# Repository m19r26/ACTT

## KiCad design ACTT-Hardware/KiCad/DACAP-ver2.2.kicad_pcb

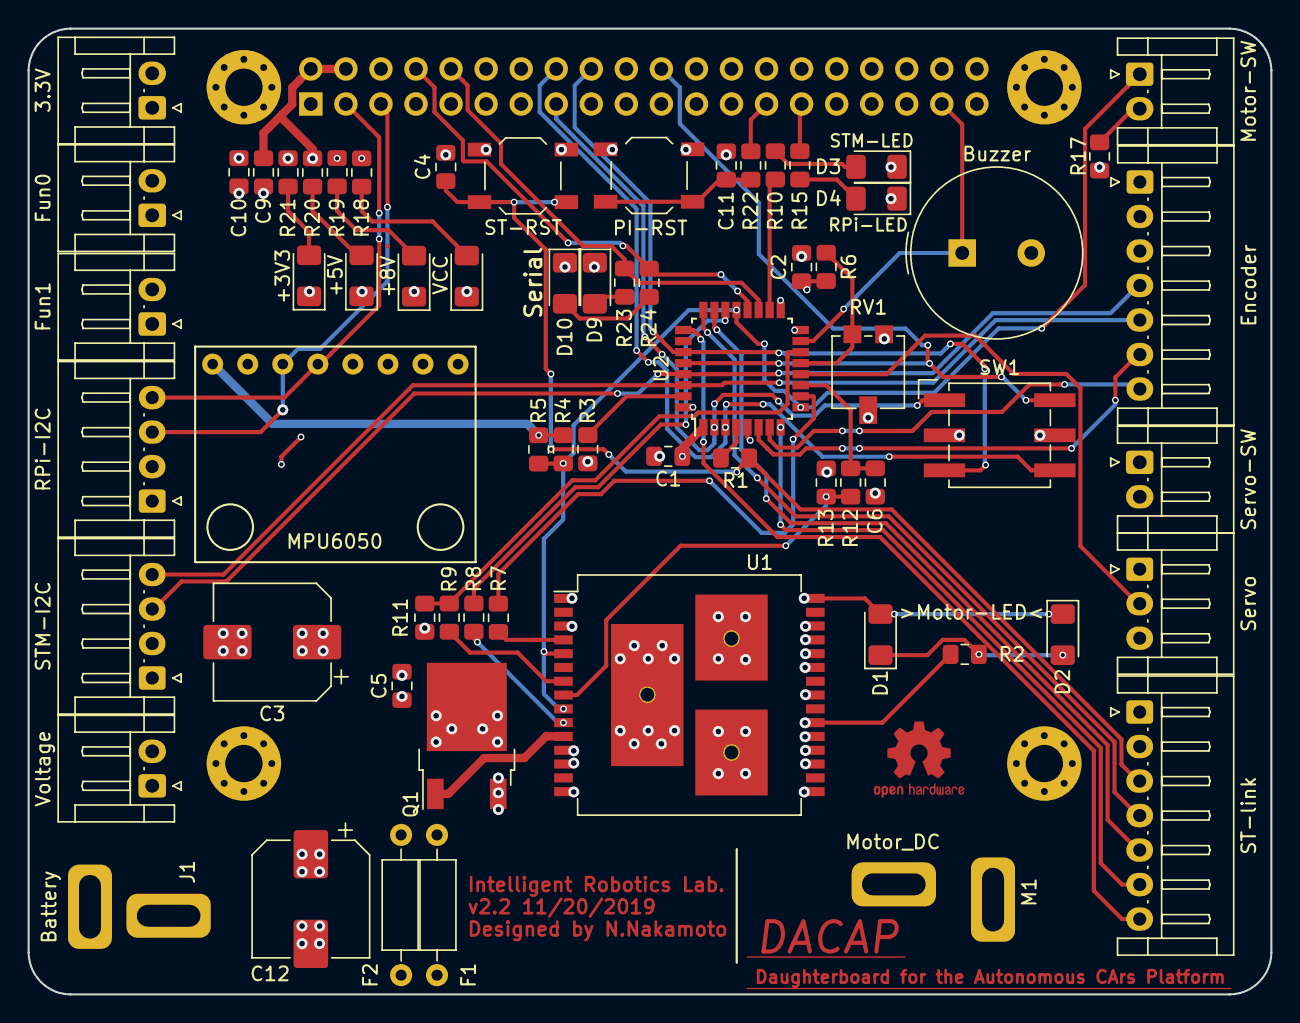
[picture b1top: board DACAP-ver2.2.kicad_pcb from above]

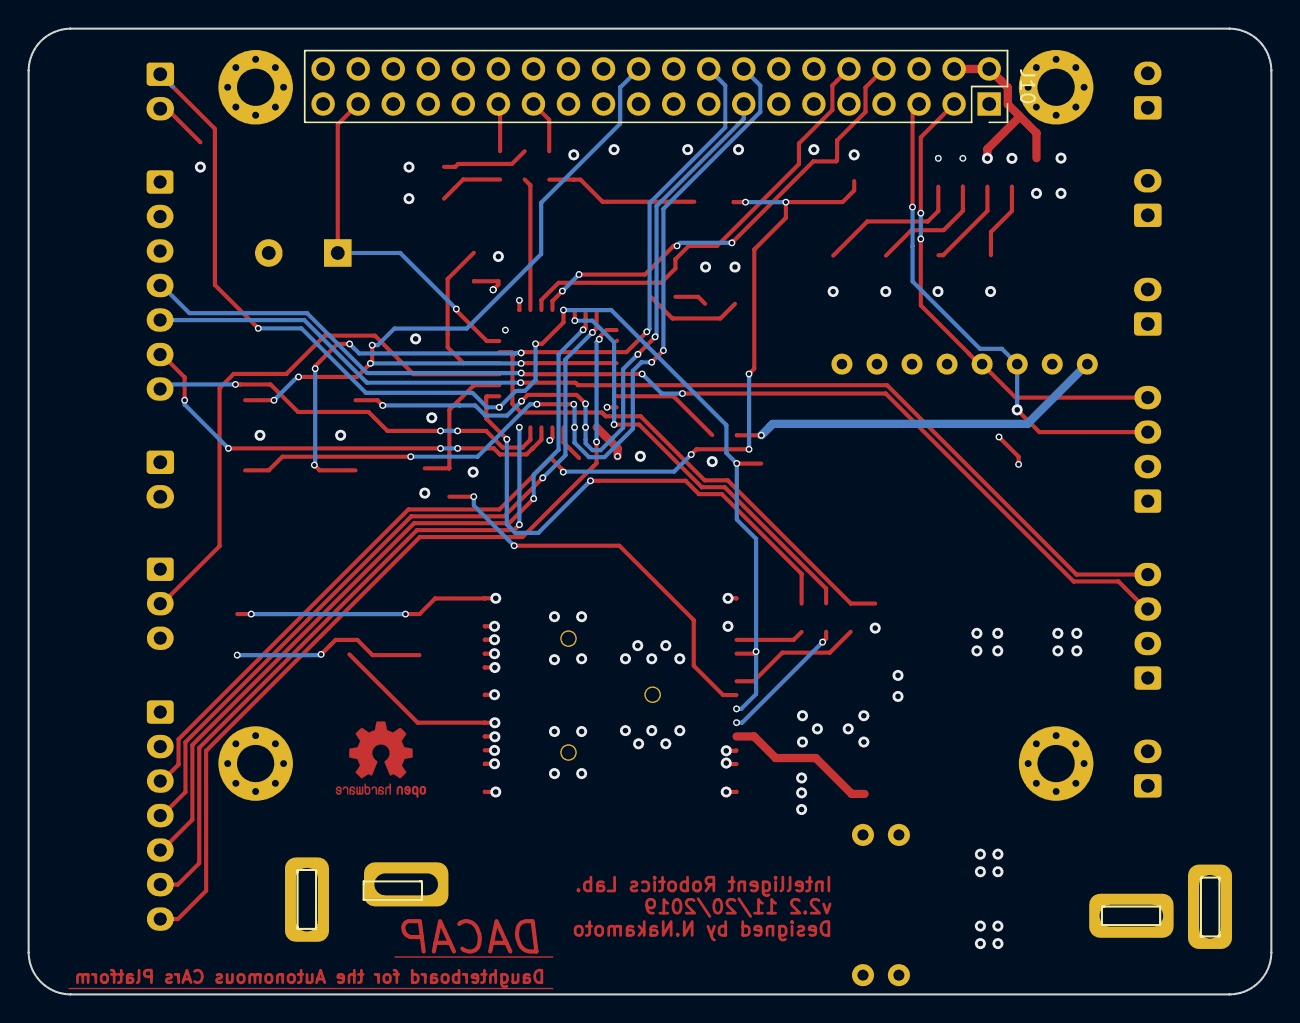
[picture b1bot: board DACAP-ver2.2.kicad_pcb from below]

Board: 4 copper layers, 90.0 x 70.0 mm, 71 parts (3 on the bottom side), 56 nets.

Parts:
3.3V: 3V3; JST_EH_S02B-EH_1x02_P2.50mm_Horizontal
Buzzer: PKM13EPYH4000-A0; Buzzer_TDK_PS1240P02BT_D12.2mm_H6.5mm
C1, C2, C4, C5, C6, C9, C10, C11: 0.1uF; C_0805_2012Metric_Pad1.15x1.40mm_HandSolder
C3, C12: 220uF; CP_Elec_8x10
D1, D9: Red-LED; LED_1206_3216Metric_Pad1.42x1.75mm_HandSolder
D2, D10: Blue-LED; LED_1206_3216Metric_Pad1.42x1.75mm_HandSolder
D3, D4: Green-LED; LED_1206_3216Metric_Pad1.42x1.75mm_HandSolder
D5: VCC; LED_1206_3216Metric_Pad1.42x1.75mm_HandSolder
D6: +8V; LED_1206_3216Metric_Pad1.42x1.75mm_HandSolder
D7: +5V; LED_1206_3216Metric_Pad1.42x1.75mm_HandSolder
D8: +3V3; LED_1206_3216Metric_Pad1.42x1.75mm_HandSolder
Encoder: Encoder; JST_EH_S07B-EH_1x07_P2.50mm_Horizontal
F1, F2: Polyfuse; R_Axial_DIN0207_L6.3mm_D2.5mm_P10.16mm_Horizontal
Fun0: Fun0; JST_EH_S02B-EH_1x02_P2.50mm_Horizontal
Fun1: Fun1; JST_EH_S02B-EH_1x02_P2.50mm_Horizontal
H1, H2, H3, H4: MountingHole; MountingHole_2.7mm_M2.5_Pad_Via
J1: Battery; Ultra_male
J10: Raspberry_Pi_2_3; PinSocket_2x20_P2.54mm_Vertical
M1: Motor_DC; Ultra_female
MPU6050: MPU6050
Motor-SW: Motor-ONOFF; JST_EH_S02B-EH_1x02_P2.50mm_Horizontal
Q1: IPD30N03S2L20ATMA1CT-ND; TO-252-2
R1, R10, R15, R20, R21, R22, R23, R24: 100; R_0805_2012Metric_Pad1.15x1.40mm_HandSolder
R2, R18, R19: 680; R_0805_2012Metric_Pad1.15x1.40mm_HandSolder
R3, R6, R7, R8, R9, R13: 1k; R_0805_2012Metric_Pad1.15x1.40mm_HandSolder
R4, R5, R17: 2.2k; R_0805_2012Metric_Pad1.15x1.40mm_HandSolder
R11, R12: 10k; R_0805_2012Metric_Pad1.15x1.40mm_HandSolder
RPi-I2C: PI-I2C; JST_EH_S04B-EH_1x04_P2.50mm_Horizontal
RV1: 50k; Potentiometer_Vishay_TS53YL_Vertical
ST-link: ST-Link; JST_EH_S07B-EH_1x07_P2.50mm_Horizontal
STM-I2C: ST-I2C; JST_EH_S04B-EH_1x04_P2.50mm_Horizontal
SW1: CT3073-1-ND; Nidec_Copal_SH-7010B
SW2: ST-RST; SW_SPST_TL3342
SW3: PI-RST; SW_SPST_TL3342
Servo: Servo; JST_EH_S03B-EH_1x03_P2.50mm_Horizontal
Servo-SW: Servo-ONOFF; JST_EH_S02B-EH_1x02_P2.50mm_Horizontal
U1: VNH5019A; ST_MultiPowerSO-30
U2: STM32F303K8T6; LQFP-32_7x7mm_P0.8mm
Voltage: voltmeter; JST_EH_S02B-EH_1x02_P2.50mm_Horizontal

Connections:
+3V3: 3.3V.2, C1.1, C2.1, C10.1, Encoder.1, Encoder.2, J10.1, J10.17, MPU6050.8, R4.1, R5.1, R6.2, R21.1, RPi-I2C.2, ST-link.2, STM-I2C.2, U2.1, U2.5, U2.17
+5V: C9.1, Fun0.2, Fun1.2, J10.2, J10.4, R20.1
+8V: F2.2, Q1.3, R19.1
+BATT: C12.1, F1.1, F2.1, J1.1, Voltage.2
CS: C6.1, R12.1, U2.11
Code0: J10.15, SW1.1, U2.2
Code1: J10.16, SW1.2, U2.3
Code2: J10.18, SW1.4, U2.27
Code3: J10.22, SW1.8, U2.28
ENA: Motor-SW.1, R4.2, R5.2, U1.5, U1.9, U2.9, U2.21
EncoderA: Encoder.6, U2.6
EncoderB: Encoder.7, U2.7
GND: 3.3V.1, Buzzer.2, C1.2, C2.2, C3.2, C4.2, C5.2, C6.2, C9.2, C10.2, C11.1, C12.2, D3.1, D4.1, D5.1, D6.1, D7.1, D8.1, D9.1, D10.1, Encoder.3, Fun0.1, Fun1.1, J1.2, J10.6, J10.9, J10.14, J10.20, J10.25, J10.30, J10.34, J10.39, MPU6050.7, R3.1, R11.2, R13.2, R17.2, RPi-I2C.1, RV1.2, RV1.3, ST-link.1, STM-I2C.1, SW1.C, SW2.1, SW3.2, Servo.1, U1.18, U1.19, U1.20, U1.26, U1.27, U1.28, U2.16, U2.32, Voltage.1
INA: R7.1, U2.10
INB: R8.1, U2.22
NRST: C4.1, R1.2, ST-link.3, SW2.2
unnamed: C11.2, R22.1, SW3.1
unnamed: D1.1, D2.2, R2.1
unnamed: D3.2, R10.2
unnamed: D4.2, R15.2
unnamed: D5.2, R18.2
unnamed: D6.2, R19.2
unnamed: D7.2, R20.2
unnamed: D8.2, R21.2
unnamed: D9.2, R23.2
unnamed: D10.2, R24.2
unnamed: J10.27, R22.2
unnamed: J10.29, R15.1
unnamed: Motor-SW.2, R17.1
unnamed: Q1.1, U1.11
unnamed: R1.1, U2.4
unnamed: R3.2, U2.31
unnamed: R6.1, RV1.1, U2.13
unnamed: R7.2, U1.4
unnamed: R8.2, U1.10
unnamed: R9.2, U1.7
unnamed: R12.2, R13.1, U1.8
OUTA: D1.2, D2.1, M1.1, U1.1, U1.25, U1.30, U1.33
OUTB: M1.2, R2.2, U1.15, U1.16, U1.21, U1.32
PI-SCL: J10.5, MPU6050.6, RPi-I2C.3
PI-SDA: J10.3, MPU6050.5, RPi-I2C.4
PWM: R9.1, R11.1, U2.14
ST-SCL: Encoder.4, STM-I2C.3, U2.29
ST-SDA: Encoder.5, STM-I2C.4, U2.30
SWCLK: ST-link.4, U2.24
SWDIO: ST-link.5, U2.23
Servo-sign: Servo.2, U2.12
UART_RXtoPI: J10.8, R24.1, U2.20
UART_TXtoPI: J10.10, R23.1, U2.19
VCC: F1.2, R18.1, Servo-SW.2
VCP_RX: ST-link.7, U2.25
VCP_TX: ST-link.6, U2.8
Vcc-servo: Servo.3, Servo-SW.1
Vout: C3.1, C5.1, Q1.2, U1.3, U1.12, U1.13, U1.23, U1.31
buzz: J10.37, U2.15
led: R10.1, U2.18

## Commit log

2021-01-27 add ACTT files
